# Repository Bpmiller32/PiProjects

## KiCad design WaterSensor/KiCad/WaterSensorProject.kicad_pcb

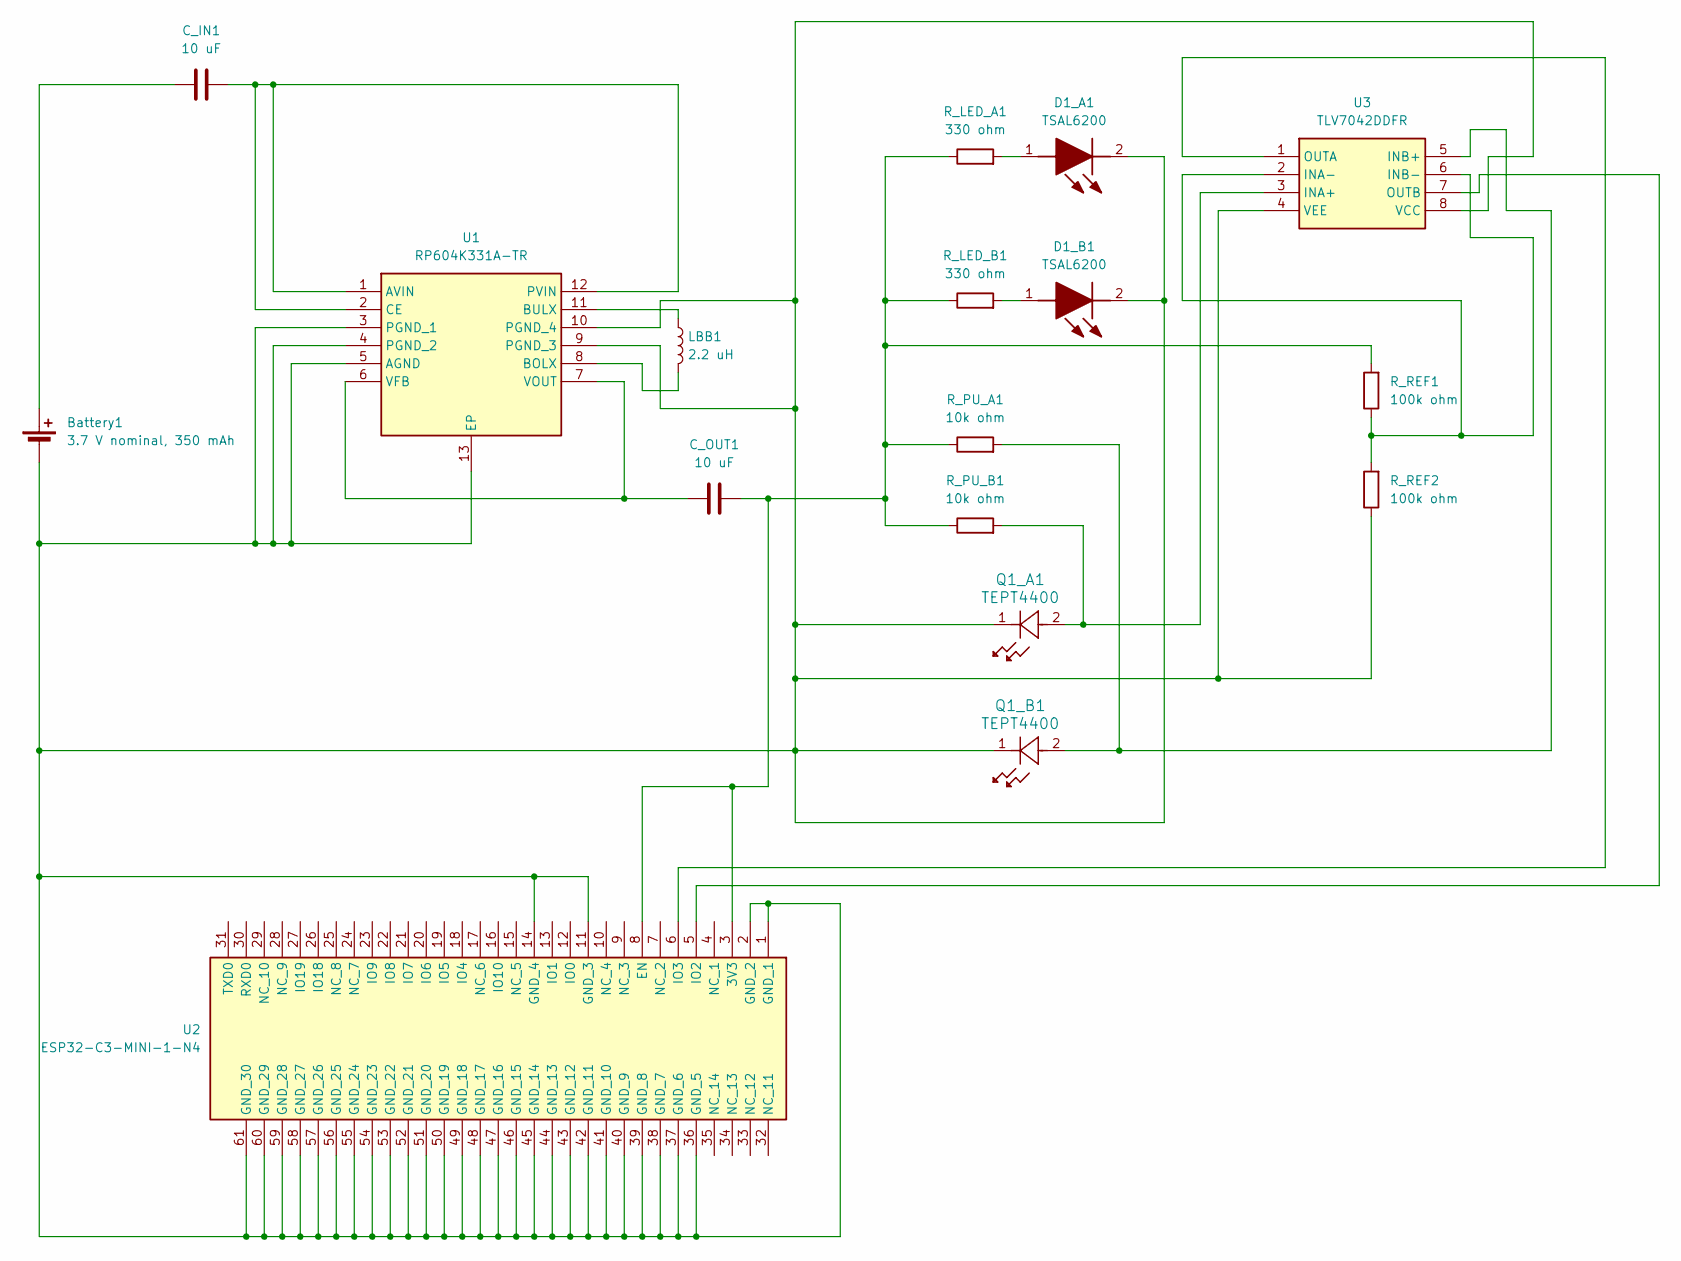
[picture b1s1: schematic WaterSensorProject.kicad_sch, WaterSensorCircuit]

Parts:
Battery1: 3.7 V nominal, 350 mAh; BatteryHolder_Keystone_2466_1xAAA
C_IN1: 10 uF; CP_Elec_3x5.3
C_OUT1: 10 uF; CP_Elec_3x5.3
D1_A1, D1_B1: TSAL6200; Mouser Part Number 782-TSAL6200
LBB1: 2.2 uH; L_6.3x6.3_H3
Q1_A1, Q1_B1: TEPT4400; LED_TEPT4400_VIS
R_LED_A1: 330 ohm; R_0201_0603Metric
R_LED_B1: 330 ohm; R_0201_0603Metric
R_PU_A1: 10k ohm; R_0201_0603Metric
R_PU_B1: 10k ohm; R_0201_0603Metric
R_REF1, R_REF2: 100k ohm; R_0201_0603Metric
U1: RP604K331A-TR; SON50P270X300X60-13N; Mouser Part Number 848-RP604K331A-TR
U2: ESP32-C3-MINI-1-N4; ESP32C3MINI1N4; Mouser Part Number 356-ESP32-C3-MINI1N4
U3: TLV7042DDFR; SOT65P280X110-8N; Mouser Part Number 595-TLV7042DDFR

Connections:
unnamed: Battery1.1 (+), C_IN1.1
unnamed: Battery1.2 (-), D1_A1.2 (K), D1_B1.2 (K), Q1_A1.1, Q1_B1.1, R_REF2.1, U1.3 (PGND_1), U1.4 (PGND_2), U1.5 (AGND), U1.9 (PGND_3), U1.10 (PGND_4), U1.13 (EP), U2.1 (GND_1), U2.2 (GND_2), U2.11 (GND_3), U2.14 (GND_4), U2.36 (GND_5), U2.37 (GND_6), U2.38 (GND_7), U2.39 (GND_8), U2.40 (GND_9), U2.41 (GND_10), U2.42 (GND_11), U2.43 (GND_12), U2.44 (GND_13), U2.45 (GND_14), U2.46 (GND_15), U2.47 (GND_16), U2.48 (GND_17), U2.49 (GND_18), U2.50 (GND_19), U2.51 (GND_20), U2.52 (GND_21), U2.53 (GND_22), U2.54 (GND_23), U2.55 (GND_24), U2.56 (GND_25), U2.57 (GND_26), U2.58 (GND_27), U2.59 (GND_28), U2.60 (GND_29), U2.61 (GND_30), U3.4 (VEE), U3.8 (VCC)
unnamed: D1_A1.1 (A), R_LED_A1.2
unnamed: D1_B1.1 (A), R_LED_B1.2
unnamed: C_IN1.2, U1.1 (AVIN), U1.2 (CE), U1.12 (PVIN)
unnamed: LBB1.2, U1.8 (BOLX)
unnamed: LBB1.1, U1.11 (BULX)
unnamed: C_OUT1.1, U1.6 (VFB), U1.7 (VOUT)
unnamed: C_OUT1.2, R_LED_A1.1, R_LED_B1.1, R_PU_A1.1, R_PU_B1.1, R_REF1.2, U2.3 (3V3), U2.8 (EN)
unnamed: U2.5 (IO2), U3.7 (OUTB)
unnamed: U2.6 (IO3), U3.1 (OUTA)
unnamed: Q1_A1.2, R_PU_B1.2, U3.3 (INA+)
unnamed: R_REF1.1, R_REF2.2, U3.2 (INA-), U3.6 (INB-)
unnamed: Q1_B1.2, R_PU_A1.2, U3.5 (INB+)

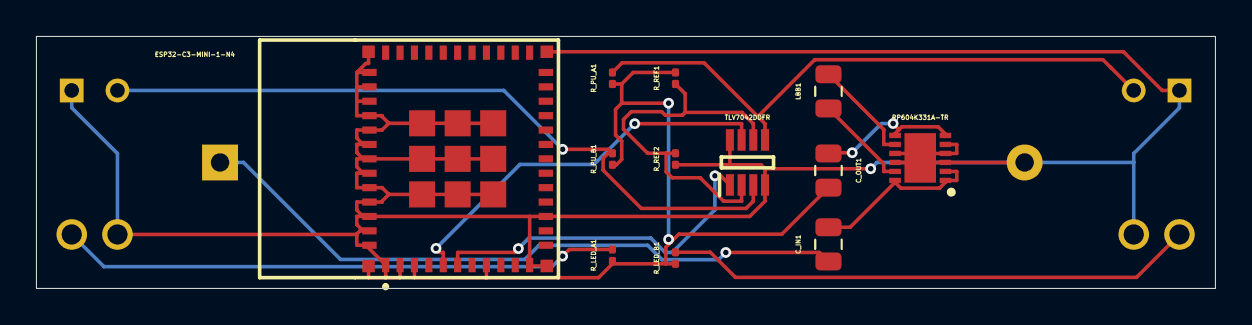
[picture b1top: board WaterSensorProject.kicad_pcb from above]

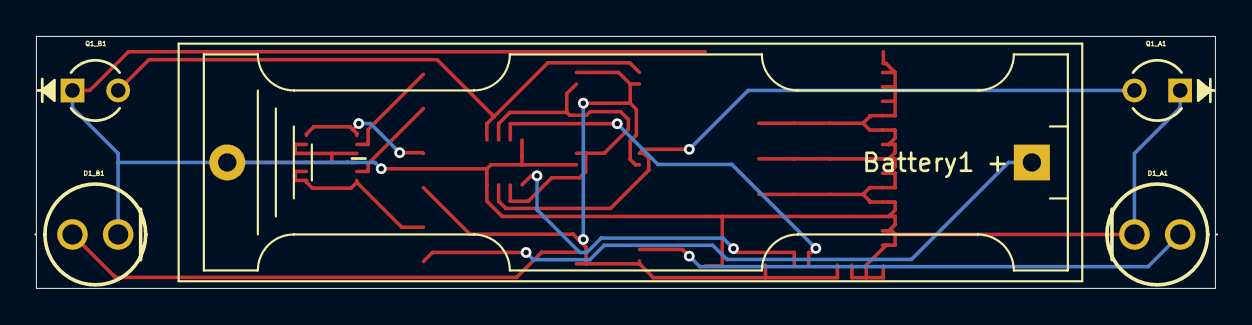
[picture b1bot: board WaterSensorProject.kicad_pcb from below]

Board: 2 copper layers, 65.5 x 14.0 mm, 17 parts (5 on the bottom side), 14 nets.

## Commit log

2022-07-04 Working initial release
2022-07-04 Fixed issue with ping turnoff, added appsettings validation
2022-07-06 Added Systemd service, small tweaks
2022-08-02 Cleanup
2022-08-30 Adding to gitignore
2023-06-13 Refactored and updated, removed the canary service project, exposed additional runtime variables to appsettings
2023-07-11 Rename and reorg of projects and files
2024-08-07 Adjusted configuration and build
2025-01-17 Added WaterSensor project, schematics + RpPico code
2025-01-22 Updated schematic, created 2 pcbs with tracks, proper footprints & models
    - Updated schematic
    - Downloaded, imported all correct footprints and models
    - Created 2 viable PCBs with tracks
2025-01-27 Alternate designs and pcbs based on different battery sizes
